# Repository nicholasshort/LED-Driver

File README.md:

# LED Driver

A USB-controlled addressable LED strip driver built to illuminate a model car display cabinet. The cabinet houses 500+ 1/43rd scale model cars across 4 vertical sections, each lit by two 120-LED strips (960 LEDs total). Any USB host can control the LEDs. For this appication, the garage includes a Raspberry Pi with a touchscreen running a web interface to send LED colour data.

<table>
  <tr>
    <td colspan="3"></td>
  </tr>
  <tr>
    <td></td>
    <td></td>
    <td></td>
  </tr>
</table>

## Hardware

- **MCU**: STM32F103RGT6 (Cortex-M3 @ 72 MHz, USB FS)
- **LEDs**: 8 × SK6812 addressable RGB strips (120 LEDs each)
- **Interface**: USB-C (CDC virtual COM port)
- **LED Control**: DMA-driven PWM for timing-critical waveform generation
- **PCB**: 4-layer, KiCad

## Repository layout

- `LED-DriverPCB/` — KiCad project (schematics, board, libraries)
- `LED-DriverPCB/Manufacturing/` — Gerbers, BOM, and pick-and-place files
- `LED-Driver-Firmware-RevB/` — STM32CubeIDE project
- `Garage-Files/` — Web control interface and startup audio

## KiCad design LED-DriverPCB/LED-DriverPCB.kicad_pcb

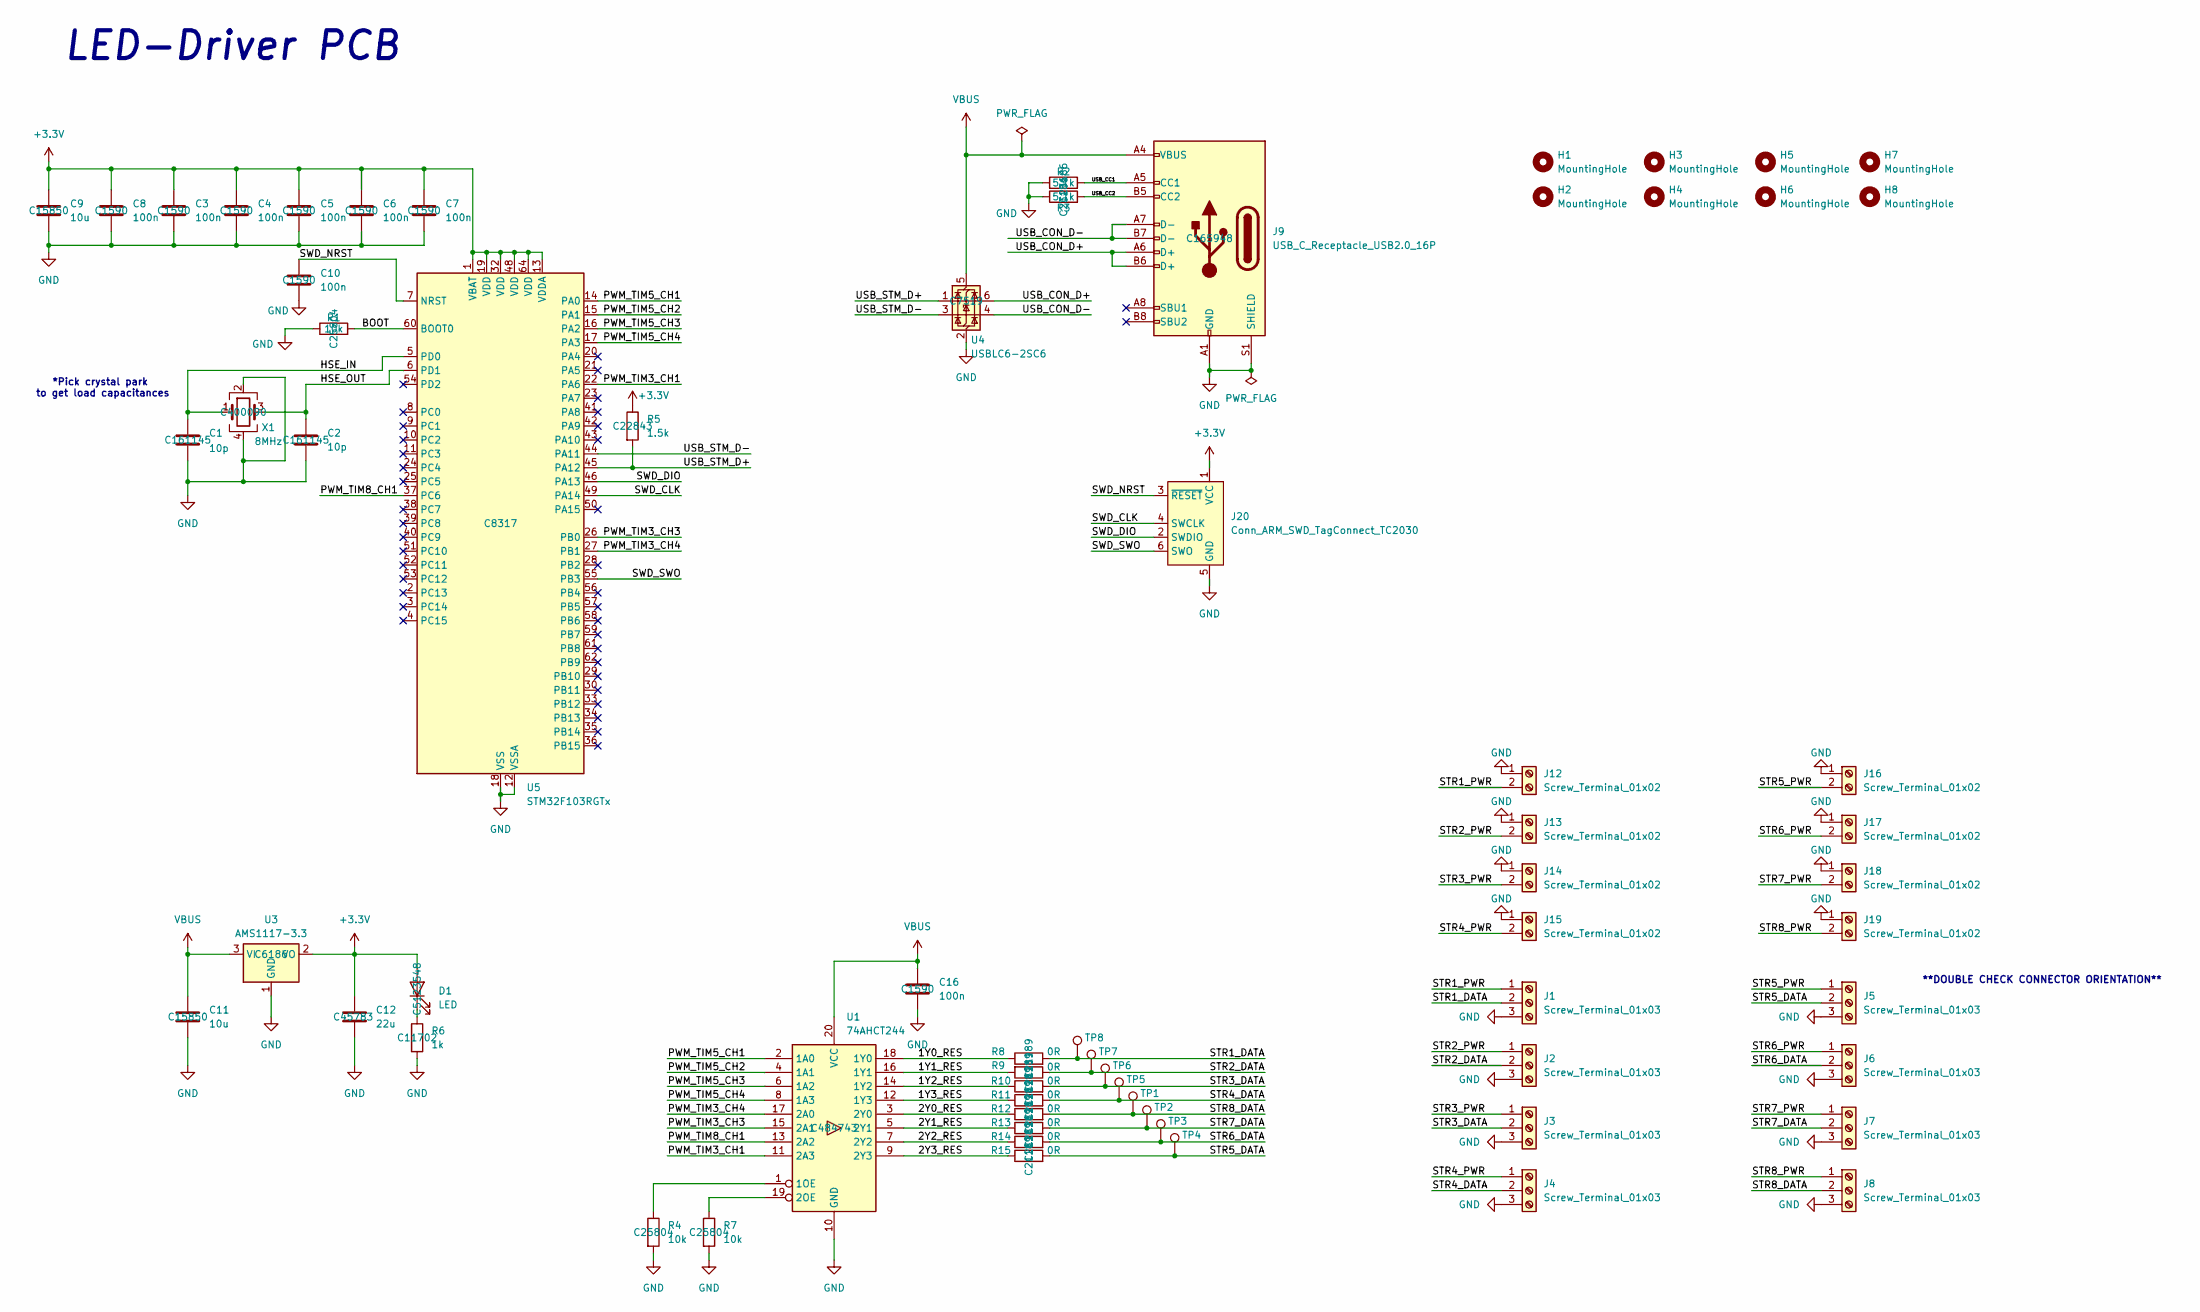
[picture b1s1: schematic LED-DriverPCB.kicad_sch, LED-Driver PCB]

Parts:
C1, C2: 10p; C_0402_1005Metric; JLCPCB Part # C161145
C3, C4, C5, C6, C7, C8, C10, C16: 100n; C_0603_1608Metric; JLCPCB Part # C1590
C9, C11: 10u; C_0805_2012Metric; JLCPCB Part # C15850
C12: 22u; C_0805_2012Metric; JLCPCB Part # C45783
D1: LED; LED_0603_1608Metric; JLCPCB Part # C5123548
H1, H2, H3, H4, H5, H6, H7, H8: MountingHole
J1, J2, J3, J4, J5, J6, J7, J8: Screw_Terminal_01x03; CONN_5569-03A4&slash_5_MOL
J9: USB_C_Receptacle_USB2.0_16P; USB_C_Receptacle_HRO_TYPE-C-31-M-12; JLCPCB Part # C165948
J12, J13, J14, J15, J16, J17, J18, J19: Screw_Terminal_01x02; CONN_5569-02A_MOL
J20: Conn_ARM_SWD_TagConnect_TC2030; Tag-Connect_TC2030-IDC-FP_2x03_P1.27mm_Vertical
R1, R4, R7: 10k; R_0603_1608Metric; JLCPCB Part # C25804
R2, R3: 5.1k; R_0603_1608Metric; JLCPCB Part # C23186
R5: 1.5k; R_0603_1608Metric; JLCPCB Part # C22843
R6: 1k; R_0402_1005Metric; JLCPCB Part # C11702
R8, R9, R10, R11, R12, R13, R14, R15: 0R; R_0603_1608Metric; JLCPCB Part # C21189
TP1, TP2, TP3, TP4, TP5, TP6, TP7, TP8: TestPoint; TestPoint_Pad_1.0x1.0mm
U1: 74AHCT244; TSSOP-20_4.4x6.5mm_P0.65mm; JLCPCB Part # C484743
U3: AMS1117-3.3; SOT-223-3_TabPin2; JLCPCB Part # C6186
U4: USBLC6-2SC6; SOT-23-6; JLCPCB Part # C7519
U5: STM32F103RGTx; LQFP-64_10x10mm_P0.5mm; JLCPCB Part # C8317
X1: 8MHz; Crystal_SMD_3225-4Pin_3.2x2.5mm; JLCPCB Part # C400090

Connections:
+3.3V: C3.1, C4.1, C5.1, C6.1, C7.1, C8.1, C9.1, C12.1, D1.2 (A), J20.1 (VCC), R5.1, U3.2 (VO), U5.1 (VBAT), U5.13 (VDDA), U5.19 (VDD), U5.32 (VDD), U5.48 (VDD), U5.64 (VDD)
/1Y0_RES: R8.1, U1.18 (1Y0)
/1Y1_RES: R9.2, U1.16 (1Y1)
/1Y2_RES: R10.1, U1.14 (1Y2)
/1Y3_RES: R11.1, U1.12 (1Y3)
/2Y0_RES: R12.1, U1.3 (2Y0)
/2Y1_RES: R13.1, U1.5 (2Y1)
/2Y2_RES: R14.1, U1.7 (2Y2)
/2Y3_RES: R15.1, U1.9 (2Y3)
/BOOT: R1.2, U5.60 (BOOT0)
/HSE_IN: C1.1, U5.5 (PD0), X1.1
/HSE_OUT: C2.1, U5.6 (PD1), X1.3
/PWM_TIM3_CH1: U1.11 (2A3), U5.22 (PA6)
/PWM_TIM3_CH3: U1.15 (2A1), U5.26 (PB0)
/PWM_TIM3_CH4: U1.17 (2A0), U5.27 (PB1)
/PWM_TIM5_CH1: U1.2 (1A0), U5.14 (PA0)
/PWM_TIM5_CH2: U1.4 (1A1), U5.15 (PA1)
/PWM_TIM5_CH3: U1.6 (1A2), U5.16 (PA2)
/PWM_TIM5_CH4: U1.8 (1A3), U5.17 (PA3)
/PWM_TIM8_CH1: U1.13 (2A2), U5.37 (PC6)
/STR1_DATA: J1.2, R8.2, TP8.1
/STR1_PWR: J1.1, J12.2
/STR2_DATA: J2.2, R9.1, TP7.1
/STR2_PWR: J2.1, J13.2
/STR3_DATA: J3.2, R10.2, TP6.1
/STR3_PWR: J3.1, J14.2
/STR4_DATA: J4.2, R11.2, TP5.1
/STR4_PWR: J4.1, J15.2
/STR5_DATA: J5.2, R15.2, TP4.1
/STR5_PWR: J5.1, J16.2
/STR6_DATA: J6.2, R14.2, TP3.1
/STR6_PWR: J6.1, J17.2
/STR7_DATA: J7.2, R13.2, TP2.1
/STR7_PWR: J7.1, J18.2
/STR8_DATA: J8.2, R12.2, TP1.1
/STR8_PWR: J8.1, J19.2
/SWD_CLK: J20.4 (SWCLK), U5.49 (PA14)
/SWD_DIO: J20.2 (SWDIO), U5.46 (PA13)
/SWD_NRST: C10.1, J20.3 (~RESET), U5.7 (NRST)
/SWD_SWO: J20.6 (SWO), U5.55 (PB3)
/USB_CC1: J9.A5 (CC1), R2.2
/USB_CC2: J9.B5 (CC2), R3.2
/USB_CON_D+: J9.A6 (D+), J9.B6 (D+), U4.6 (I/O1)
/USB_CON_D-: J9.A7 (D-), J9.B7 (D-), U4.4 (I/O2)
/USB_STM_D+: R5.2, U4.1 (I/O1), U5.45 (PA12)
/USB_STM_D-: U4.3 (I/O2), U5.44 (PA11)
GND: C1.2, C2.2, C3.2, C4.2, C5.2, C6.2, C7.2, C8.2, C9.2, C10.2, C11.2, C12.2, C16.2, J1.3, J2.3, J3.3, J4.3, J5.3, J6.3, J7.3, J8.3, J9.A1 (GND), J9.A12 (GND), J9.B1 (GND), J9.B12 (GND), J9.S1 (SHIELD), J12.1, J13.1, J14.1, J15.1, J16.1, J17.1, J18.1, J19.1, J20.5 (GND), R1.1, R2.1, R3.1, R4.2, R6.2, R7.2, U1.10 (GND), U3.1 (GND), U4.2 (GND), U5.12 (VSSA), U5.18 (VSS), U5.31 (VSS), U5.47 (VSS), U5.63 (VSS), X1.2, X1.4
unnamed: D1.1 (K), R6.1
unnamed: R4.1, U1.1 (1OE)
unnamed: R7.1, U1.19 (2OE)
VBUS: C11.1, C16.1, J9.A4 (VBUS), J9.A9 (VBUS), J9.B4 (VBUS), J9.B9 (VBUS), U1.20 (VCC), U3.3 (VI), U4.5 (VBUS)

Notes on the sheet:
LED-Driver PCB
*Pick crystal park to get load capacitances
**DOUBLE CHECK CONNECTOR ORIENTATION**

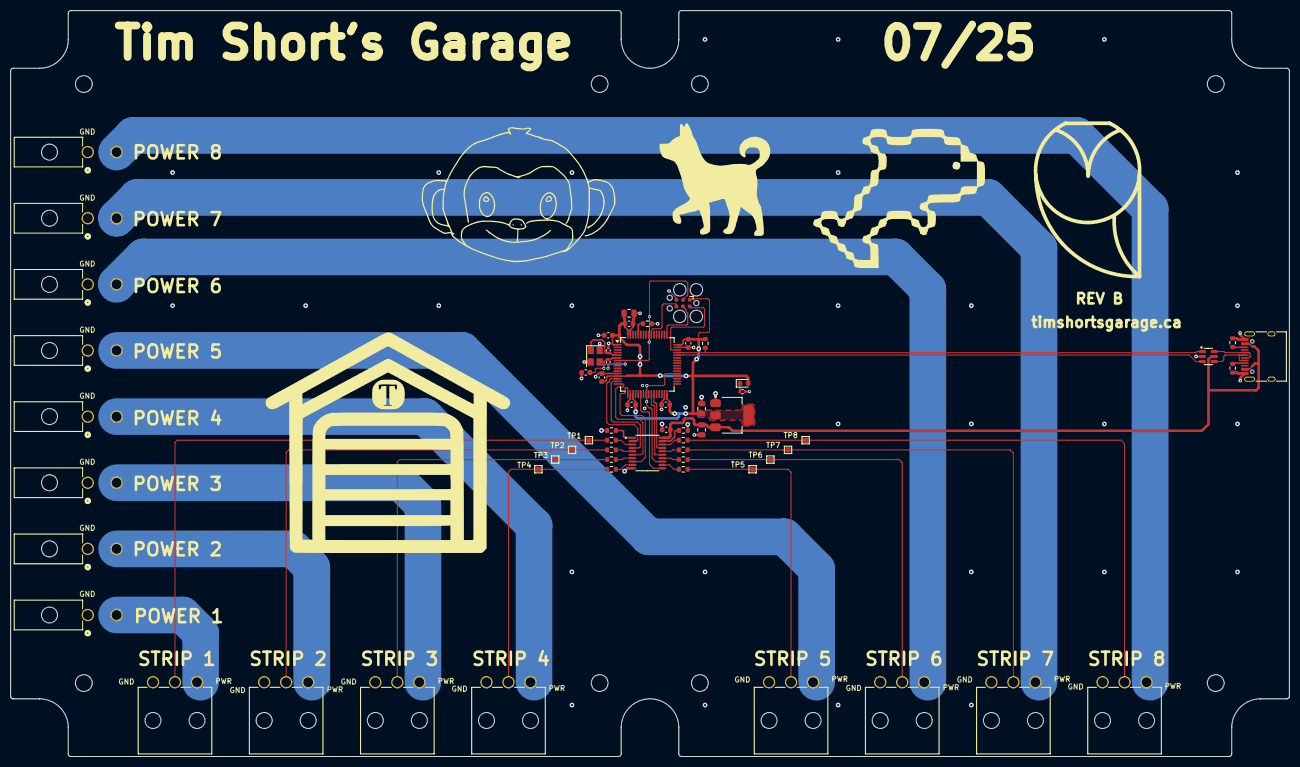
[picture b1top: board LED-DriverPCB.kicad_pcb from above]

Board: 4 copper layers, 244.0 x 142.3 mm, 68 parts (0 on the bottom side), 51 nets.

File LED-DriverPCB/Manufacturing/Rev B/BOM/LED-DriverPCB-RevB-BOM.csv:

"Reference","Value","Footprint","Qty","JLCPCB Part #"
"H1","MountingHole","","1",""
"H2","MountingHole","","1",""
"H3","MountingHole","","1",""
"H4","MountingHole","","1",""
"H5","MountingHole","","1",""
"H6","MountingHole","","1",""
"H7","MountingHole","","1",""
"H8","MountingHole","","1",""
"J1","Screw_Terminal_01x03","39303037:CONN_5569-03A4&slash_5_MOL","1",""
"J2","Screw_Terminal_01x03","39303037:CONN_5569-03A4&slash_5_MOL","1",""
"J3","Screw_Terminal_01x03","39303037:CONN_5569-03A4&slash_5_MOL","1",""
"J4","Screw_Terminal_01x03","39303037:CONN_5569-03A4&slash_5_MOL","1",""
"J5","Screw_Terminal_01x03","39303037:CONN_5569-03A4&slash_5_MOL","1",""
"J6","Screw_Terminal_01x03","39303037:CONN_5569-03A4&slash_5_MOL","1",""
"J7","Screw_Terminal_01x03","39303037:CONN_5569-03A4&slash_5_MOL","1",""
"J8","Screw_Terminal_01x03","39303037:CONN_5569-03A4&slash_5_MOL","1",""
"J12","Screw_Terminal_01x02","26013114:CONN_5569-02A_MOL","1",""
"J13","Screw_Terminal_01x02","26013114:CONN_5569-02A_MOL","1",""
"J14","Screw_Terminal_01x02","26013114:CONN_5569-02A_MOL","1",""
"J15","Screw_Terminal_01x02","26013114:CONN_5569-02A_MOL","1",""
"J16","Screw_Terminal_01x02","26013114:CONN_5569-02A_MOL","1",""
"J17","Screw_Terminal_01x02","26013114:CONN_5569-02A_MOL","1",""
"J18","Screw_Terminal_01x02","26013114:CONN_5569-02A_MOL","1",""
"J19","Screw_Terminal_01x02","26013114:CONN_5569-02A_MOL","1",""
"J20","Conn_ARM_SWD_TagConnect_TC2030","Connector:Tag-Connect_TC2030-IDC-FP_2x03_P1.27mm_Vertical","1",""
"TP1","TestPoint","TestPoint:TestPoint_Pad_1.0x1.0mm","1",""
"TP2","TestPoint","TestPoint:TestPoint_Pad_1.0x1.0mm","1",""
"TP3","TestPoint","TestPoint:TestPoint_Pad_1.0x1.0mm","1",""
"TP4","TestPoint","TestPoint:TestPoint_Pad_1.0x1.0mm","1",""
"TP5","TestPoint","TestPoint:TestPoint_Pad_1.0x1.0mm","1",""
"TP6","TestPoint","TestPoint:TestPoint_Pad_1.0x1.0mm","1",""
"TP7","TestPoint","TestPoint:TestPoint_Pad_1.0x1.0mm","1",""
"TP8","TestPoint","TestPoint:TestPoint_Pad_1.0x1.0mm","1",""
"C3","100n","Capacitor_SMD:C_0603_1608Metric","1","C1590"
"C4","100n","Capacitor_SMD:C_0603_1608Metric","1","C1590"
"C5","100n","Capacitor_SMD:C_0603_1608Metric","1","C1590"
"C6","100n","Capacitor_SMD:C_0603_1608Metric","1","C1590"
"C7","100n","Capacitor_SMD:C_0603_1608Metric","1","C1590"
"C8","100n","Capacitor_SMD:C_0603_1608Metric","1","C1590"
"C10","100n","Capacitor_SMD:C_0603_1608Metric","1","C1590"
"C16","100n","Capacitor_SMD:C_0603_1608Metric","1","C1590"
"U3","AMS1117-3.3","Package_TO_SOT_SMD:SOT-223-3_TabPin2","1","C6186"
"U4","USBLC6-2SC6","Package_TO_SOT_SMD:SOT-23-6","1","C7519"
"U5","STM32F103RGTx","Package_QFP:LQFP-64_10x10mm_P0.5mm","1","C8317"
"R6","1k","Resistor_SMD:R_0402_1005Metric","1"," C11702"
"C9","10u","Capacitor_SMD:C_0805_2012Metric","1","C15850"
"C11","10u","Capacitor_SMD:C_0805_2012Metric","1","C15850"
"R8","0R","Resistor_SMD:R_0603_1608Metric","1","C21189"
"R9","0R","Resistor_SMD:R_0603_1608Metric","1","C21189"
"R10","0R","Resistor_SMD:R_0603_1608Metric","1","C21189"
"R11","0R","Resistor_SMD:R_0603_1608Metric","1","C21189"
"R12","0R","Resistor_SMD:R_0603_1608Metric","1","C21189"
"R13","0R","Resistor_SMD:R_0603_1608Metric","1","C21189"
"R14","0R","Resistor_SMD:R_0603_1608Metric","1","C21189"
"R15","0R","Resistor_SMD:R_0603_1608Metric","1","C21189"
"R5","1.5k","Resistor_SMD:R_0603_1608Metric","1","C22843"
"R2","5.1k","Resistor_SMD:R_0603_1608Metric","1","C23186"
"R3","5.1k","Resistor_SMD:R_0603_1608Metric","1","C23186"
"R1","10k","Resistor_SMD:R_0603_1608Metric","1"," C25804"
"R4","10k","Resistor_SMD:R_0603_1608Metric","1"," C25804"
"R7","10k","Resistor_SMD:R_0603_1608Metric","1"," C25804"
"C12","22u","Capacitor_SMD:C_0805_2012Metric","1","C45783"
"C1","10p","Capacitor_SMD:C_0402_1005Metric","1","C161145"
"C2","10p","Capacitor_SMD:C_0402_1005Metric","1","C161145"
"J9","USB_C_Receptacle_USB2.0_16P","Connector_USB:USB_C_Receptacle_HRO_TYPE-C-31-M-12","1","C165948"
"X1","8MHz","Crystal:Crystal_SMD_3225-4Pin_3.2x2.5mm","1","C400090"
"U1","74AHCT244","Package_SO:TSSOP-20_4.4x6.5mm_P0.65mm","1","C484743"
"D1","LED","LED_SMD:LED_0603_1608Metric","1","C5123548"

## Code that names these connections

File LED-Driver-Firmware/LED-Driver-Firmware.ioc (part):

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Mcu.Name=STM32F103R(C-D-E)Tx
Mcu.Package=LQFP64
Mcu.UserName=STM32F103RCTx
PA0-WKUP.Signal=S_TIM5_CH1
PA1.Signal=S_TIM5_CH2
PA11.Mode=Device
PA11.Signal=USB_DM
PA12.Mode=Device
PA12.Signal=USB_DP
PA13.Mode=Trace_Asynchronous_SW
PA13.Signal=SYS_JTMS-SWDIO
PA14.Mode=Trace_Asynchronous_SW
PA14.Signal=SYS_JTCK-SWCLK
PA2.Signal=S_TIM5_CH3
PA3.Signal=S_TIM5_CH4
PA6.Signal=S_TIM3_CH1
PB0.Signal=S_TIM3_CH3
PB1.Signal=S_TIM3_CH4
PB3.Mode=Trace_Asynchronous_SW
PB3.Signal=SYS_JTDO-TRACESWO
PC6.Signal=S_TIM8_CH1
PD0-OSC_IN.Mode=HSE-External-Oscillator
PD0-OSC_IN.Signal=RCC_OSC_IN
PD1-OSC_OUT.Mode=HSE-External-Oscillator
PD1-OSC_OUT.Signal=RCC_OSC_OUT
RCC.SYSCLKFreq_VALUE=72000000
RCC.SYSCLKSource=RCC_SYSCLKSOURCE_PLLCLK
board=custom

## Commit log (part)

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2025-04-30 Adding STM32F1 nucleo board working code for one LED strip
2025-04-30 Updating gitignore
2025-04-30 Created new PCB files and added KiCAD gitignore config
2025-05-08 Updating gitignore to ignore .settings folder from cubeide
2025-05-08 Picked out MCU and added it to schematic
2025-05-08 Adding STM32CubeIDE files
2025-05-09 Created symbol library and PCM2704C symbol
2025-05-10 Finished MCU connections
2025-06-02 Finished schematic
2025-06-02 Added footprints
2025-06-02 Worked on PCB layout
2025-06-03 Rough layout completed
2025-06-09 Finished edge cuts
2025-06-09 Placed parts
2025-06-10 Small changes
2025-06-11 Aligned connectors
2025-06-11 Started routing
2025-06-14 More routing
2025-06-18 Finalized layout
2025-06-20 Finished PCB
2025-06-20 Created manufaturing files
2025-07-13 Added code to get LED strip 1 port to run pink bouncing light program. Has not been tested on LED strip - simply testing to see if I can upload code
2025-07-20 Working USB VCP transmit!
2025-07-20 Working Rx and Tx!
2025-07-21 Refactored SK6812 driver to control multiple LED strips via a strip handle
2025-07-24 Changed MCU and level shifter
2025-07-24 Added schematic for new level shifter
2025-07-27 fixed bugs
2025-07-28 Fixed issues
2025-07-28 Added garage logo
2025-07-28 Created manufacturing files
2025-08-08 Adding new Firmware project for PCB RevB
2025-08-09 Transitioning away from cubeide. Using makefile now instead
2025-08-09 Trimming all the fat
2025-08-09 Editing gitignore to ignore build files
2025-08-09 Ignoring .vscode
2025-08-09 Added makefile debug target to run gdb and connect to openocd
2025-08-09 Remove .DS_Store files and update .gitignore
2025-08-09 Added .DS_Store to gitignore
2025-08-09 Nice green pattern thingy
2025-08-09 Added LEDStrip Manager component to manage multiple led strips. Tested out driver atop car garage. 5/8 led strips working
2025-12-06 Added LED startup sequence
2025-12-06 Added USB_DEVICE middleware to project
2025-12-06 Working LED usb control protocol with python script to test
2025-12-06 Added led control webpage
2025-12-07 Adding garage intro music. Also changing to 5fps to prevent flickering, and adding a warmer orange default colour
2025-12-07 Playing audio only when connected to stm32
2026-04-04 Adding startup animation synced with audio
2026-04-04 Updating fps from 5 to 10
